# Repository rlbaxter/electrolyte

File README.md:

# Electrolyte 10x4 Ortholinear Keyboard PCB

## Firmware

- [QMK](https://github.com/rlbaxter/qmk_firmware/tree/electrolyte/keyboards/rlbaxter/electrolyte)
- [ZMK](https://github.com/rlbaxter/zmk/tree/electrolyte/app/boards/shields/electrolyte)

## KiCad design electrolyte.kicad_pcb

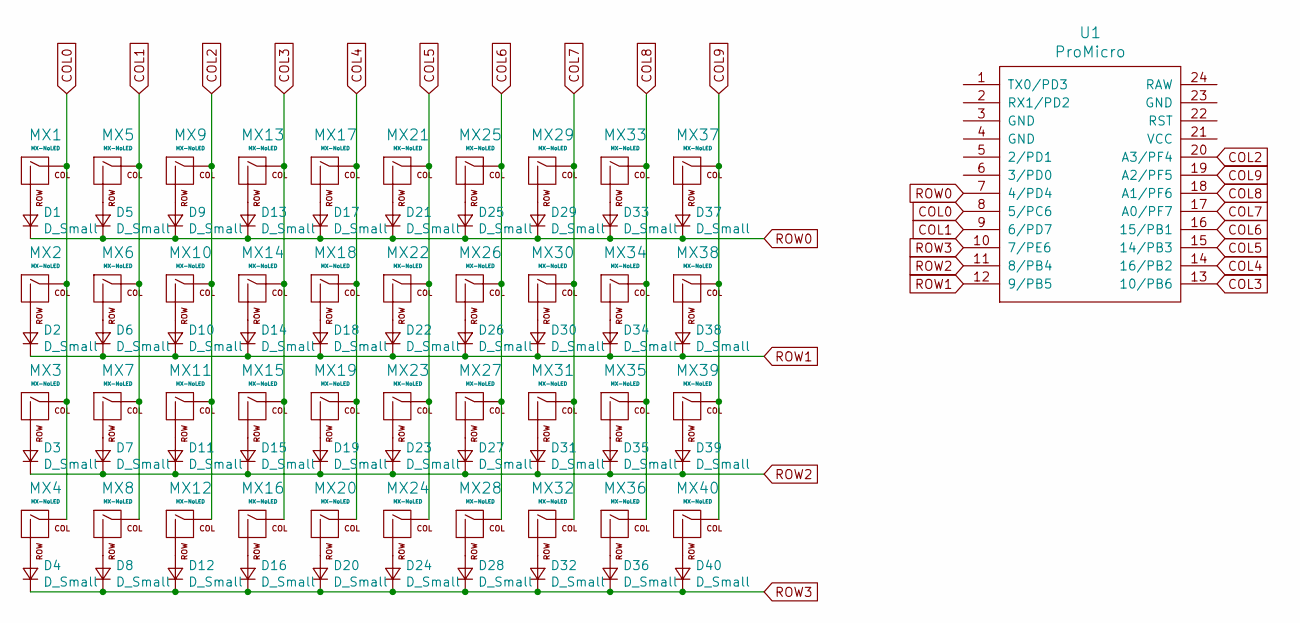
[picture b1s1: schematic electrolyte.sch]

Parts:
D1, D2, D3, D4, D5, D6, D7, D8, D9, D10, D11, D12, D13, D14, D15, D16, D17, D18, D19, D20, D21, D22, D23, D24, D25, D26, D27, D28, D29, D30, D31, D32, D33, D34, D35, D36, D37, D38, D39, D40: D_Small; Diode-Hybrid-Back
MX1, MX2, MX3, MX4, MX5, MX6, MX7, MX8, MX9, MX10, MX11, MX12, MX13, MX14, MX15, MX16, MX17, MX18, MX19, MX20, MX21, MX22, MX23, MX24, MX25, MX26, MX27, MX28, MX29, MX30, MX31, MX32, MX33, MX34, MX35, MX36, MX37, MX38, MX39, MX40: MX-NoLED; MXOnly-1U-NoLED
U1: ProMicro; ArduinoProMicro

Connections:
COL0: MX1.1 (COL), MX2.1 (COL), MX3.1 (COL), MX4.1 (COL), U1.8 (5/PC6)
COL1: MX5.1 (COL), MX6.1 (COL), MX7.1 (COL), MX8.1 (COL), U1.9 (6/PD7)
COL2: MX9.1 (COL), MX10.1 (COL), MX11.1 (COL), MX12.1 (COL), U1.20 (A3/PF4)
COL3: MX13.1 (COL), MX14.1 (COL), MX15.1 (COL), MX16.1 (COL), U1.13 (10/PB6)
COL4: MX17.1 (COL), MX18.1 (COL), MX19.1 (COL), MX20.1 (COL), U1.14 (16/PB2)
COL5: MX21.1 (COL), MX22.1 (COL), MX23.1 (COL), MX24.1 (COL), U1.15 (14/PB3)
COL6: MX25.1 (COL), MX26.1 (COL), MX27.1 (COL), MX28.1 (COL), U1.16 (15/PB1)
COL7: MX29.1 (COL), MX30.1 (COL), MX31.1 (COL), MX32.1 (COL), U1.17 (A0/PF7)
COL8: MX33.1 (COL), MX34.1 (COL), MX35.1 (COL), MX36.1 (COL), U1.18 (A1/PF6)
COL9: MX37.1 (COL), MX38.1 (COL), MX39.1 (COL), MX40.1 (COL), U1.19 (A2/PF5)
unnamed: D1.2 (A), MX1.2 (ROW)
unnamed: D2.2 (A), MX2.2 (ROW)
unnamed: D3.2 (A), MX3.2 (ROW)
unnamed: D4.2 (A), MX4.2 (ROW)
unnamed: D5.2 (A), MX5.2 (ROW)
unnamed: D6.2 (A), MX6.2 (ROW)
unnamed: D7.2 (A), MX7.2 (ROW)
unnamed: D8.2 (A), MX8.2 (ROW)
unnamed: D9.2 (A), MX9.2 (ROW)
unnamed: D10.2 (A), MX10.2 (ROW)
unnamed: D11.2 (A), MX11.2 (ROW)
unnamed: D12.2 (A), MX12.2 (ROW)
unnamed: D13.2 (A), MX13.2 (ROW)
unnamed: D14.2 (A), MX14.2 (ROW)
unnamed: D15.2 (A), MX15.2 (ROW)
unnamed: D16.2 (A), MX16.2 (ROW)
unnamed: D17.2 (A), MX17.2 (ROW)
unnamed: D18.2 (A), MX18.2 (ROW)
unnamed: D19.2 (A), MX19.2 (ROW)
unnamed: D20.2 (A), MX20.2 (ROW)
unnamed: D21.2 (A), MX21.2 (ROW)
unnamed: D22.2 (A), MX22.2 (ROW)
unnamed: D23.2 (A), MX23.2 (ROW)
unnamed: D24.2 (A), MX24.2 (ROW)
unnamed: D25.2 (A), MX25.2 (ROW)
unnamed: D26.2 (A), MX26.2 (ROW)
unnamed: D27.2 (A), MX27.2 (ROW)
unnamed: D28.2 (A), MX28.2 (ROW)
unnamed: D29.2 (A), MX29.2 (ROW)
unnamed: D30.2 (A), MX30.2 (ROW)
unnamed: D31.2 (A), MX31.2 (ROW)
unnamed: D32.2 (A), MX32.2 (ROW)
unnamed: D33.2 (A), MX33.2 (ROW)
unnamed: D34.2 (A), MX34.2 (ROW)
unnamed: D35.2 (A), MX35.2 (ROW)
unnamed: D36.2 (A), MX36.2 (ROW)
unnamed: D37.2 (A), MX37.2 (ROW)
unnamed: D38.2 (A), MX38.2 (ROW)
unnamed: D39.2 (A), MX39.2 (ROW)
unnamed: D40.2 (A), MX40.2 (ROW)
ROW0: D1.1 (K), D5.1 (K), D9.1 (K), D13.1 (K), D17.1 (K), D21.1 (K), D25.1 (K), D29.1 (K), D33.1 (K), D37.1 (K), U1.7 (4/PD4)
ROW1: D2.1 (K), D6.1 (K), D10.1 (K), D14.1 (K), D18.1 (K), D22.1 (K), D26.1 (K), D30.1 (K), D34.1 (K), D38.1 (K), U1.12 (9/PB5)
ROW2: D3.1 (K), D7.1 (K), D11.1 (K), D15.1 (K), D19.1 (K), D23.1 (K), D27.1 (K), D31.1 (K), D35.1 (K), D39.1 (K), U1.11 (8/PB4)
ROW3: D4.1 (K), D8.1 (K), D12.1 (K), D16.1 (K), D20.1 (K), D24.1 (K), D28.1 (K), D32.1 (K), D36.1 (K), D40.1 (K), U1.10 (7/PE6)

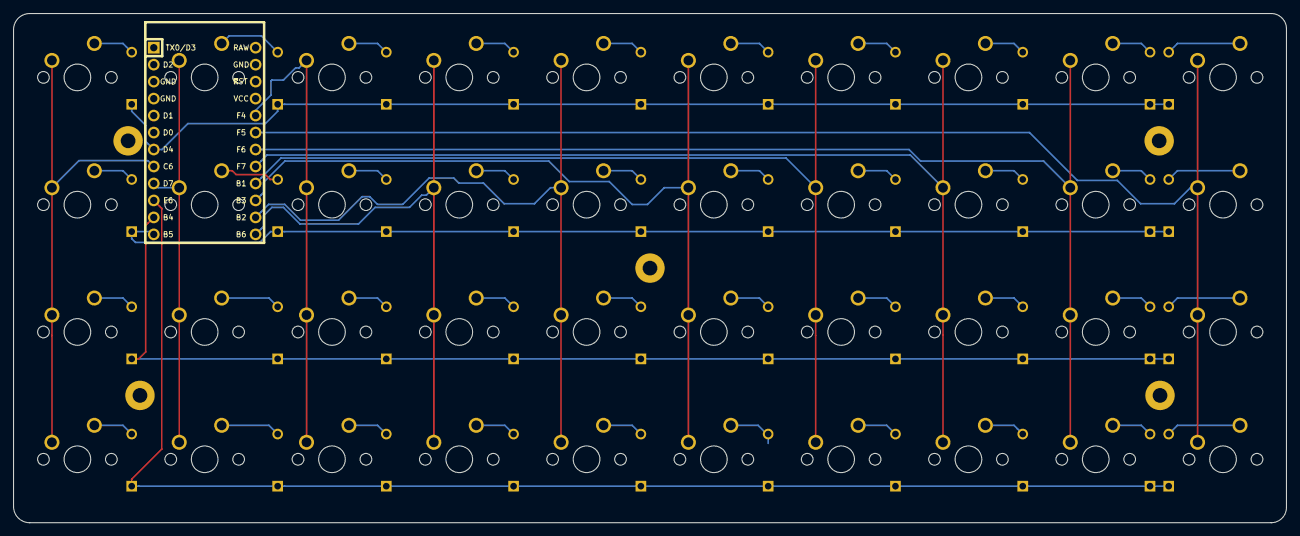
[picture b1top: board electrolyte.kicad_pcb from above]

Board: 2 copper layers, 190.5 x 76.2 mm, 82 parts (0 on the bottom side), 54 nets.

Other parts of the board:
x_x: MountingHole_2.2mm_M2_Pad

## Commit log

2021-02-21 plop
2021-02-21 add submodules
2021-02-21 add footprints and symbols
2021-02-21 save work in progress
2021-02-22 more work on the design
2021-02-23 finish up v1, pcbs are ordered
2021-03-06 updates and added readme
2021-09-02 add license
2022-03-16 add the link to the zmk firmware
2024-07-01 update qmk link
